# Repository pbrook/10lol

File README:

10LOL display board (10mm rgb led charlieplexed display matrix)
====

Hardware designs and firmware for a modular matrix display board.

Each module consists of an LED carrier board and a driver board.

Supply voltage is 7-20V (with onboard switching regulator).
TODO: Figure out actual power requirements, and if a single regulator can power
multiple modules.

The control board 
Modules operate autonomously,  module operates autonomously, accepting data over SPI.
The modules can be programmed with unique addresses, allowing
multiple modules on a single SPI bus.

SPI communication protocol
====

Commands are 4 bytes.  The first byte identidies the command, followed by 3
bytes of argument data (d0-d2).

On power-up the board will be in disconnected state.  A disconnect command
followed by a connect command should be used to ensure the serial interface
is coherent, and the board is in the ready state.

Command 0xe1 puts the specified board into the active state (other
previously active boards return to the ready state).

Commands <0xd0 are ignored when the board is not active.

Commands are as follows:

0x00 - 0x3f: Write pixel
 Pixels numbered left-right,then top-bottom)
  d0: red
  d1: green
  d2: blue

0x80: Page flip
 Set the framebuffer page for both display and pixel writing.
 This allows double buffered updates
  d0: Unused(0)
  d1: display page number
  d2: pixel write page number

0xa0: Initialize FORTH
 Initialize and enable the FORTH interpreter.
 The forth dictionary is stored at the end of the framebuffer.
  d0: rstack size (cells)
  d1: Dictionary size (in 256-byte framebuffer pages)
  d2: Unused (0)

0xa1: FORTH source
 Send one to three bytes of FORTH source code.  Null (0) characters are ignored.
  d0: First character
  d1: Second character
  d2: Third character

0xc0: Set brightness
 Sets brightness/color ballance (stored in EEPROM)
  d0: Red brightness
  d1: Green brightness
  d2: Blue brightness

0xd0: Set board address
 Modifies the board address (stored in EEPROM).
 The board will only respond to this address if the SDA pin is pulled low.
 This allows the addresses to be set without disconnecting the board.
  d0: 0xf5
  d1: 0xf0 + high address nibble
  d2: 0xf0 + low address nibble

0xe0: Connect
 Prepares the board for other commands
  d0: 0xf0
  d1: 0xf1
  d2: 0xf2

0xe1: Board select
 Only the selected board will respond to most commands.
  d0: board address (0xff to select all boards)
  d1: Unused (0)
  d2: Unused (0)

0xff: Disconnect
 Reset serial interface.
 The connect command must be sent before any other commands.
 The data bytes on this command are optional.  However sending the full
 sequence bytes ensures that the board is preoperly aligned with the
 four byte command boundary.
  d0: 0xff
  d1: 0xff
  d2: 0xff

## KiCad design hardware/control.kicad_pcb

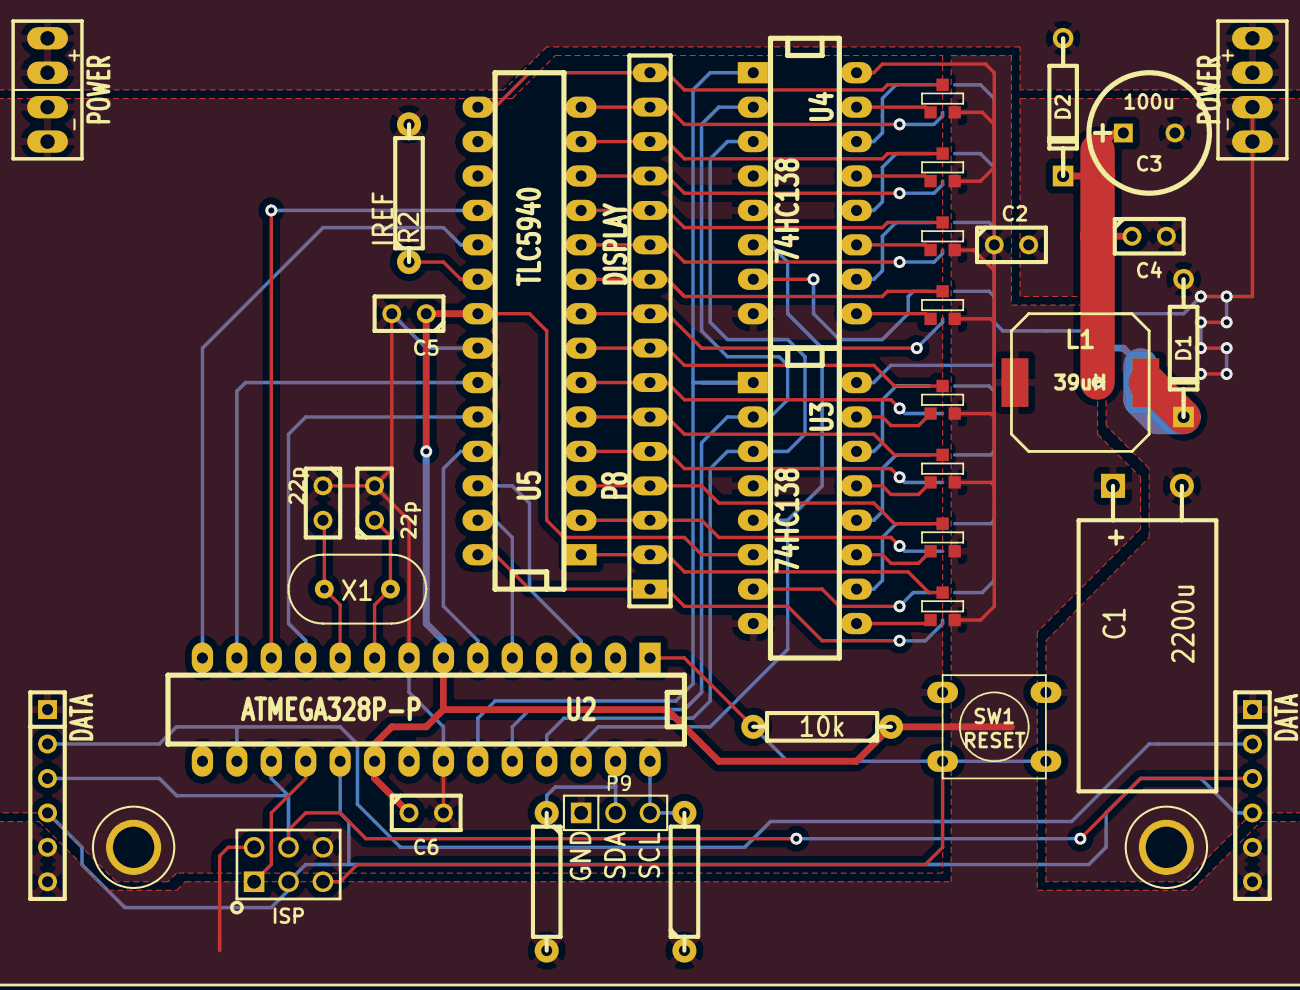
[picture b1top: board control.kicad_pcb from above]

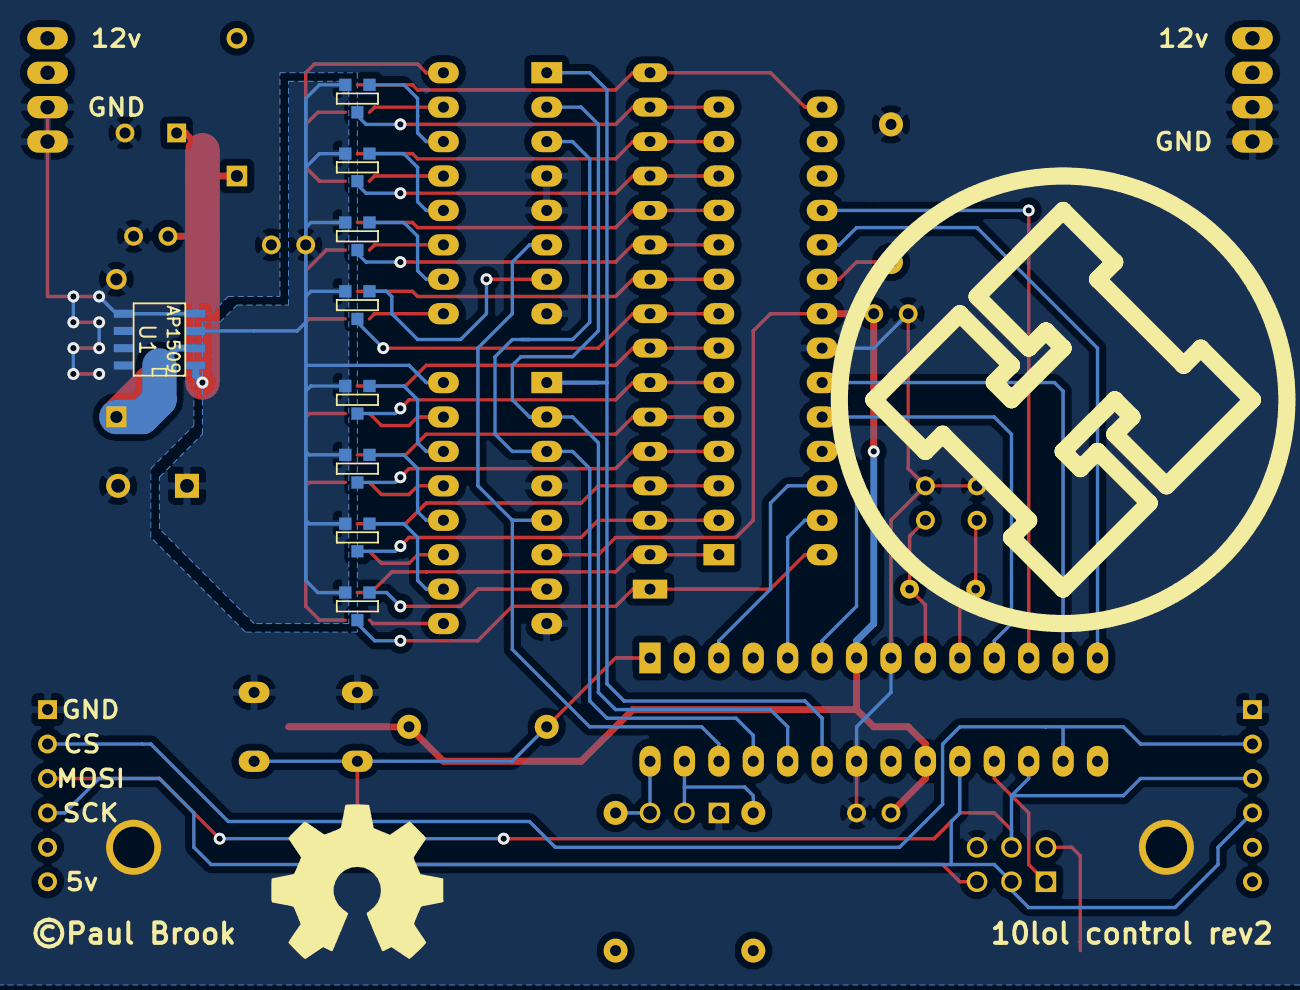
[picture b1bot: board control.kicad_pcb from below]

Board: 2 copper layers, 48 parts (10 on the bottom side), 58 nets.

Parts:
C1: 2200u; CPR10X20
C2, C4, C5, C6: 100n; C1
C3: 100u; C1.5V8V
C8, C9: 22p; C1
D1, D2: SR104; DO-41
HACKSPACE_LOGO: VAL**; HACKSPACE_LOGO
L1: 39uH; self_cms_we-tpc_XL
P1, P2: POWER; power2
P3, P4: DATA; SIL-6
P5: ISP; isp
P6, P7: CONN_1; HOLE3
P8: DISPLAY; SIL-16-ELL
P9: I2C; PIN_ARRAY_3X1
Q1, Q2, Q3, Q4, Q5, Q6, Q7, Q8, Q9, Q10, Q11, Q12, Q13, Q14, Q15, Q16: NX2301P; SOT23GDS_NP
R1: 10k; R4-LARGE_PADS
R2: IREF; R4-LARGE_PADS
R3: SDA; R4-LARGE_PADS
R4: SCL; R4-LARGE_PADS
SW1: RESET; SW_PUSH_SMALL
U1: AP1509; SO8E
U2: ATMEGA328P-P; DIP-28__300_ELL
U3, U4: 74HC138; DIP-16__300_ELL
U5: TLC5940; DIP-28__300_ELL
X1: 16MHz; Crystal

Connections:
/5v: C1.1, C2.1, C5.1, C6.1, L1.1, P3.5, P3.6, P4.5, P4.6, P5.2, Q1.S, Q2.S, Q3.S, Q4.S, Q5.S, Q6.S, Q7.S, Q8.S, Q9.S, Q10.S, Q11.S, Q12.S, Q13.S, Q14.S, Q15.S, Q16.S, R1.1, R3.2, R4.1, U1.3, U2.7, U2.20, U3.6, U3.16, U4.16, U5.21
/12v: C3.1, C4.1, D2.2, U1.1
/A: P8.1, Q1.D, U5.28
/A0: U2.23, U3.1, U4.1
/A1: U2.24, U3.2, U4.2
/A2: U2.25, U3.3, U4.3
/A3: U2.26, U3.5, U4.6
/Ai: Q1.G, U3.7
/B: P8.2, Q2.D, U5.1
/BLANK: U2.13, U5.23
/Bi: Q2.G, U3.9
/C: P8.3, Q3.D, U5.2
/CS: P3.2, P4.2, U2.16
/Ci: Q3.G, U3.10
/D: P8.4, Q4.D, U5.3
/DCPRG: U2.14, U5.19
/Di: Q4.G, U3.11
/E: P8.5, Q5.D, U5.4
/Ei: Q5.G, U3.12
/F: P8.6, Q6.D, U5.5
/Fi: Q6.G, U3.13
/G: P8.7, Q7.D, U5.6
/GND: C1.2, C2.2, C3.2, C4.2, C5.2, C6.2, C8.2, C9.1, D1.1, P1.1, P2.1, P3.1, P4.1, P5.6, P6.1, P7.1, P9.1, R2.2, SW1.1, U1.4, U1.5, U1.6, U1.7, U1.8, U2.8, U2.22, U3.4, U3.8, U4.4, U4.5, U4.8, U5.22
/GSCLK: U2.12, U5.18
/Gi: Q7.G, U3.14
/H: P8.8, Q8.D, U5.7
/Hi: Q8.G, U3.15
/IREF: R2.1, U5.20
/J: P8.9, Q9.D, U5.8
/Ji: Q9.G, U4.7
/K: P8.10, Q10.D, U5.9
/Ki: Q10.G, U4.9
/M: P8.11, Q11.D, U5.10
/MISO: P5.1, U2.18
/MOSI: P3.3, P4.3, P5.4, U2.17
/Mi: Q11.G, U4.10
/N: P8.12, Q12.D, U5.11
/Ni: Q12.G, U4.11
/P: P8.13, Q13.D, U5.12
/Pi: Q13.G, U4.12
/Q: P8.14, Q14.D, U5.13
/Qi: Q14.G, U4.13
/R: P8.15, Q15.D, U5.14
/RESET: P5.5, R1.2, SW1.2, U2.1
/Ri: Q15.G, U4.14
/S: P8.16, Q16.D, U5.15
/SCK: P3.4, P4.4, P5.3, U2.19
/SCL: P9.3, R4.2, U2.28
/SCLK: U2.6, U5.25
/SDA: P9.2, R3.1, U2.27
/SIN: U2.3, U5.26
/Si: Q16.G, U4.15
/VPRG: U2.5, U5.27
/XLAT: U2.11, U5.24
/out: D1.2, L1.2, U1.2
/raw: D2.1, P1.2, P2.2
unnamed: C9.2, U2.10, X1.1
unnamed: C8.1, U2.9, X1.2

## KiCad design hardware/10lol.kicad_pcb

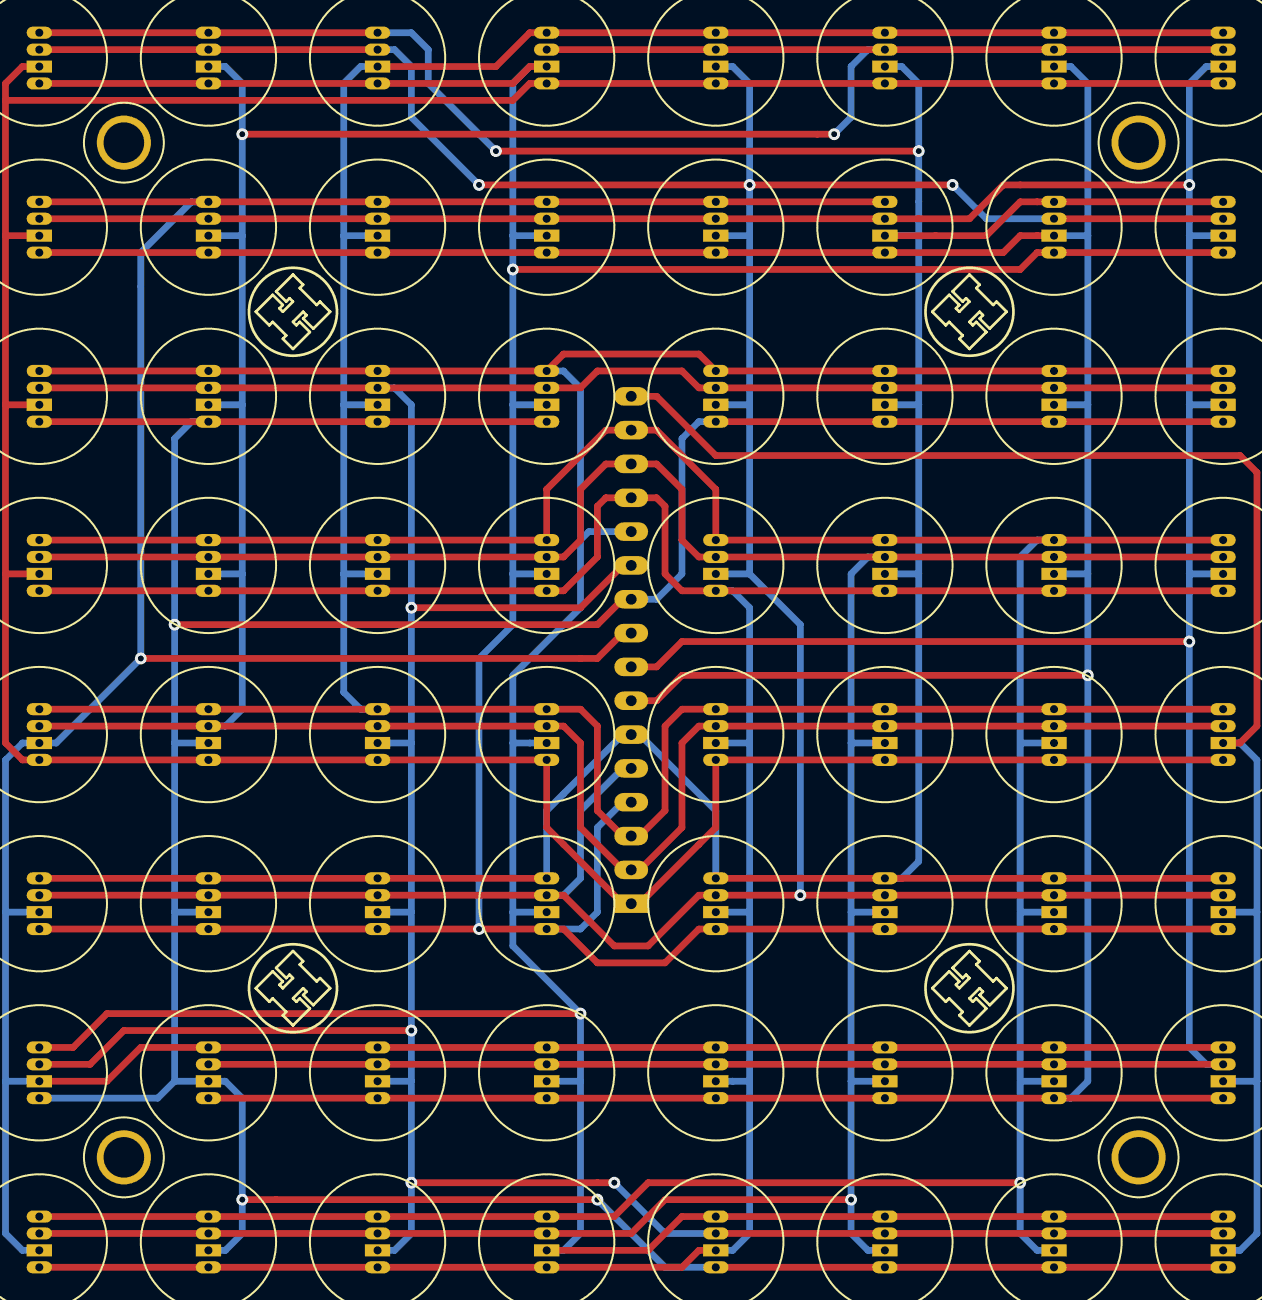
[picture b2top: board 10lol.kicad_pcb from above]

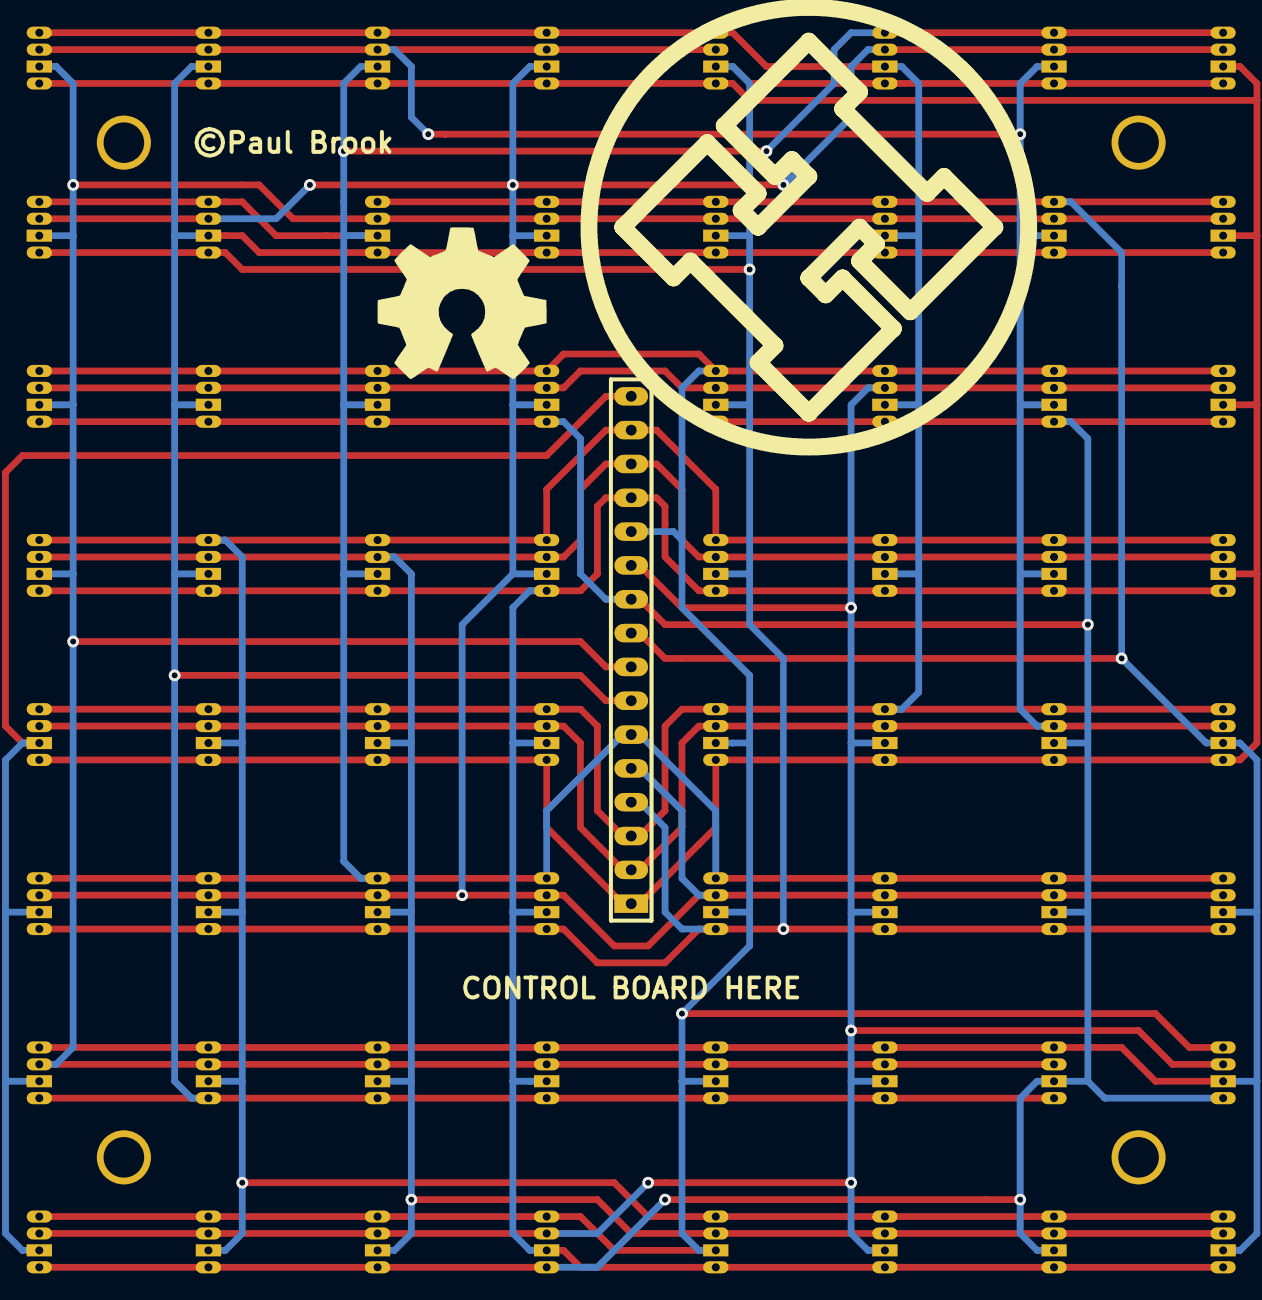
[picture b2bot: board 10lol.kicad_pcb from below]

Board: 2 copper layers, 74 parts (2 on the bottom side), 16 nets.

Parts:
D1, D2, D3, D4, D5, D6, D7, D8, D9, D10, D11, D12, D13, D14, D15, D16, D17, D18, D19, D20, D21, D22, D23, D24, D25, D26, D27, D28, D29, D30, D31, D32, D33, D34, D35, D36, D37, D38, D39, D40, D41, D42, D43, D44, D45, D46, D47, D48, D49, D50, D51, D52, D53, D54, D55, D56, D57, D58, D59, D60, D61, D62, D63, D64: RGBLED; RGB_LED_10_S
HACKSPACE_LOGO: VAL**; HACKSPACE_LOGO
LOGO_SMALL1: LOGO_S1; LOGO_SMALL
LOGO_SMALL2: LOGO_S2; LOGO_SMALL
LOGO_SMALL3: LOGO_S3; LOGO_SMALL
LOGO_SMALL4: LOGO_S4; LOGO_SMALL
P1: CONN_16; SIL-16-ELL
P2, P3, P4, P5: CONN_1; HOLE3

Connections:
/A: D1.2, D2.2, D3.2, D4.2, D5.1, D13.1, D21.1, D25.1, D29.1, D33.1, D37.1, D41.1, D45.1, D49.1, D53.1, D57.1, D61.1, P1.1
/B: D5.3, D9.2, D10.2, D11.2, D12.2, D13.3, D21.3, D25.3, D29.3, D33.3, D37.3, D41.3, D45.3, D49.3, D53.3, D57.3, D61.3, P1.2
/C: D5.4, D13.4, D17.2, D18.2, D19.2, D20.2, D21.4, D25.4, D29.4, D33.4, D37.4, D41.4, D45.4, D49.4, D53.4, D57.4, D61.4, P1.3
/D: D1.1, D6.1, D9.1, D14.1, D17.1, D22.1, D25.2, D26.2, D27.2, D28.2, D30.1, D38.1, D46.1, D50.1, D54.1, D58.1, D62.1, P1.4
/E: D1.3, D6.3, D9.3, D14.3, D17.3, D22.3, D30.3, D33.2, D34.2, D35.2, D36.2, D38.3, D46.3, D50.3, D54.3, D58.3, D62.3, P1.5
/F: D1.4, D6.4, D9.4, D14.4, D17.4, D22.4, D30.4, D38.4, D41.2, D42.2, D43.2, D44.2, D46.4, D50.4, D54.4, D58.4, D62.4, P1.6
/G: D2.1, D10.1, D15.1, D18.1, D23.1, D26.1, D31.1, D34.1, D39.1, D42.1, D47.1, D49.2, D50.2, D51.2, D52.2, D55.1, D63.1, P1.7
/H: D2.3, D10.3, D15.3, D18.3, D23.3, D26.3, D31.3, D34.3, D39.3, D42.3, D47.3, D55.3, D57.2, D58.2, D59.2, D60.2, D63.3, P1.8
/J: D2.4, D5.2, D6.2, D7.2, D8.2, D10.4, D15.4, D18.4, D23.4, D26.4, D31.4, D34.4, D39.4, D42.4, D47.4, D55.4, D63.4, P1.9
/K: D3.1, D7.1, D11.1, D13.2, D14.2, D15.2, D16.2, D19.1, D27.1, D35.1, D40.1, D43.1, D48.1, D51.1, D56.1, D59.1, D64.1, P1.10
/M: D3.3, D7.3, D11.3, D19.3, D21.2, D22.2, D23.2, D24.2, D27.3, D35.3, D40.3, D43.3, D48.3, D51.3, D56.3, D59.3, D64.3, P1.11
/N: D3.4, D7.4, D11.4, D19.4, D27.4, D29.2, D30.2, D31.2, D32.2, D35.4, D40.4, D43.4, D48.4, D51.4, D56.4, D59.4, D64.4, P1.12
/P: D4.1, D8.1, D12.1, D16.1, D20.1, D24.1, D28.1, D32.1, D36.1, D37.2, D38.2, D39.2, D40.2, D44.1, D52.1, D60.1, P1.13
/Q: D4.3, D8.3, D12.3, D16.3, D20.3, D24.3, D28.3, D32.3, D36.3, D44.3, D45.2, D46.2, D47.2, D48.2, D52.3, D60.3, P1.14
/R: D4.4, D8.4, D12.4, D16.4, D20.4, D24.4, D28.4, D32.4, D36.4, D44.4, D52.4, D53.2, D54.2, D55.2, D56.2, D60.4, P1.15
/S: D61.2, D62.2, D63.2, D64.2, P1.16

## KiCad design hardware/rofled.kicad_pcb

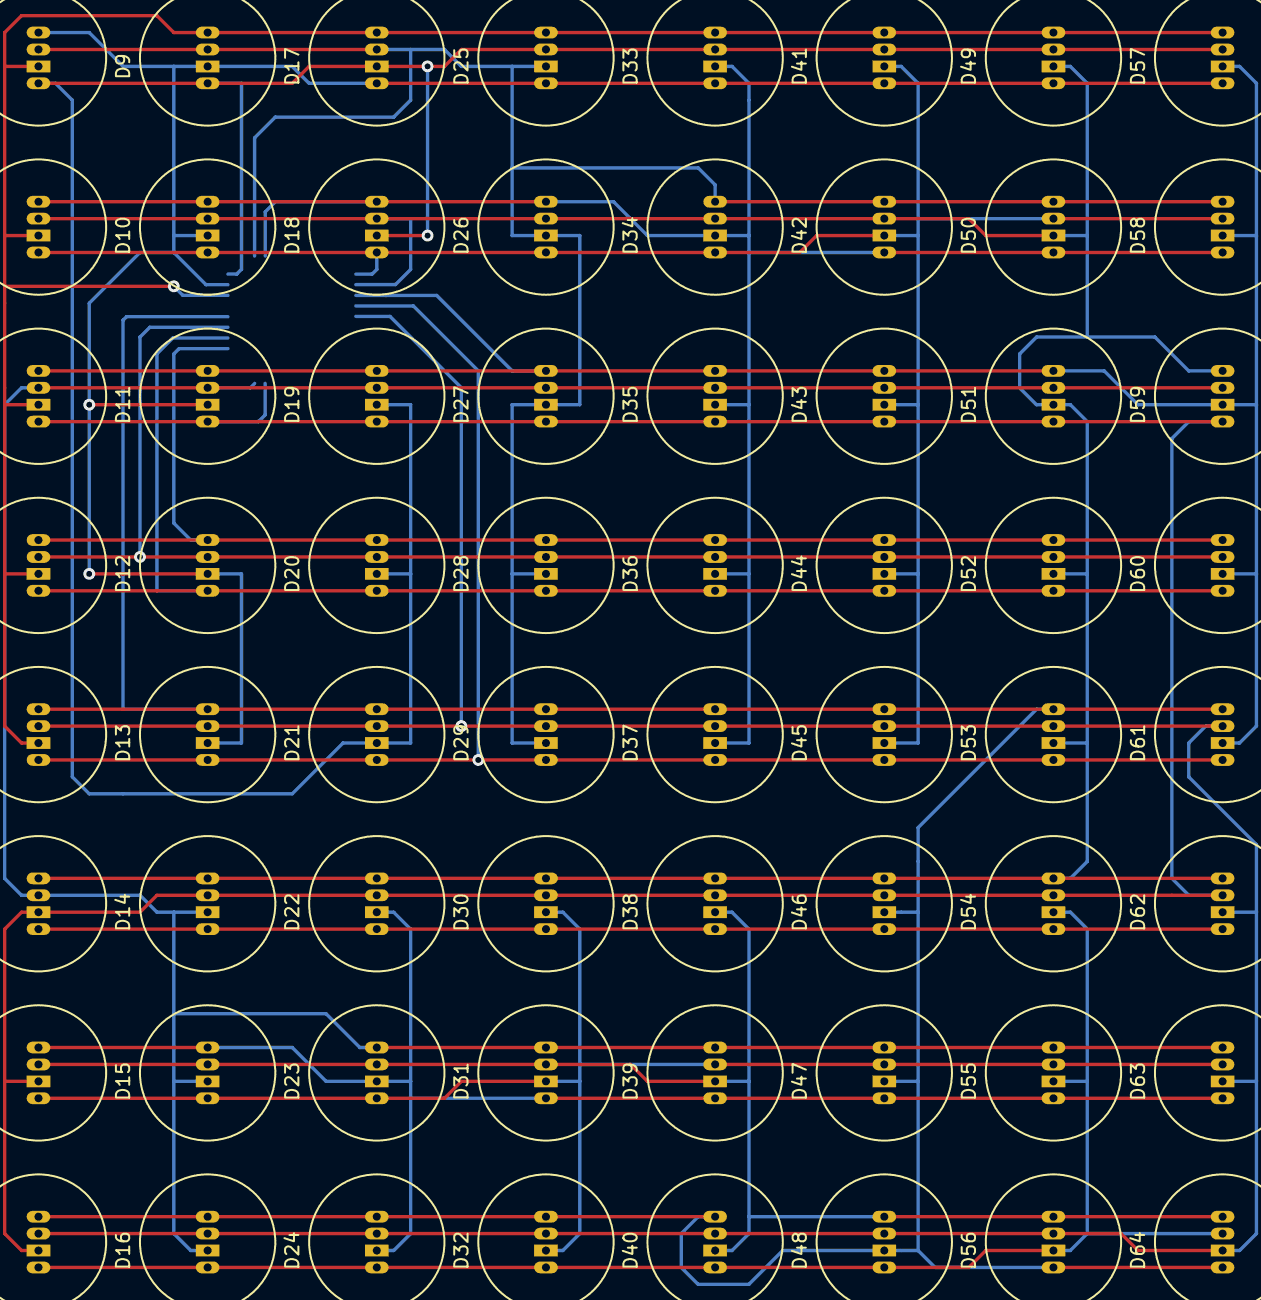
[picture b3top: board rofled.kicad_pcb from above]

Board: 2 copper layers, 65 parts (1 on the bottom side), 16 nets.

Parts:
D1, D2, D3, D4, D5, D6, D7, D8, D9, D10, D11, D12, D13, D14, D15, D16, D17, D18, D19, D20, D21, D22, D23, D24, D25, D26, D27, D28, D29, D30, D31, D32, D33, D34, D35, D36, D37, D38, D39, D40, D41, D42, D43, D44, D45, D46, D47, D48, D49, D50, D51, D52, D53, D54, D55, D56, D57, D58, D59, D60, D61, D62, D63, D64: RGBLED; RGB_LED_10
IC1: ATMEGA328P-A; TQFP32

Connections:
/A: D1.2, D2.2, D3.2, D4.2, D5.2, D9.4, D17.4, D25.4, D33.4, D41.4, D49.4, D57.4, IC1.30
/B: D1.4, D9.2, D10.2, D11.2, D12.2, D13.2, D17.1, D25.1, D33.1, D41.1, D49.1, D57.1, IC1.31
/C: D1.1, D9.1, D17.2, D18.2, D19.2, D20.2, D21.2, D25.3, D33.3, D41.3, D49.3, D57.3, IC1.32
/D: D1.3, D9.3, D17.3, D25.2, D26.2, D27.2, D28.2, D29.2, D34.4, D42.4, D50.4, D58.4, IC1.1
/E: D2.4, D10.4, D18.4, D26.4, D33.2, D34.2, D35.2, D36.2, D37.2, D42.1, D50.1, D58.1, IC1.2
/F: D2.1, D10.1, D18.1, D26.1, D34.1, D41.2, D42.2, D43.2, D44.2, D45.2, D50.3, D58.3, IC1.9
/G: D2.3, D6.4, D10.3, D14.4, D18.3, D22.4, D26.3, D30.4, D34.3, D38.4, D42.3, D46.4, D49.2, D50.2, D51.2, D52.2, D53.2, D54.4, D59.4, D62.4, IC1.10
/H: D3.4, D6.1, D11.4, D14.1, D19.4, D22.1, D27.4, D30.1, D35.4, D38.1, D43.4, D46.1, D51.4, D54.1, D57.2, D58.2, D59.2, D60.2, D61.2, D62.1, IC1.11
/J: D3.1, D6.2, D7.2, D8.2, D11.1, D14.3, D19.1, D22.3, D27.1, D30.3, D35.1, D38.3, D43.1, D46.3, D51.1, D54.3, D59.1, D62.3, IC1.23
/K: D3.3, D6.3, D11.3, D14.2, D15.2, D16.2, D19.3, D23.4, D27.3, D31.4, D35.3, D39.4, D43.3, D47.4, D51.3, D55.4, D59.3, D63.4, IC1.24
/M: D4.4, D7.4, D12.4, D15.4, D20.4, D22.2, D23.2, D24.2, D28.4, D31.1, D36.4, D39.1, D44.4, D47.1, D52.4, D55.1, D60.4, D63.1, IC1.25
/N: D4.1, D7.1, D12.1, D15.1, D20.1, D23.1, D28.1, D30.2, D31.2, D32.2, D36.1, D39.3, D44.1, D47.3, D52.1, D55.3, D60.1, D63.3, IC1.26
/P: D4.3, D7.3, D12.3, D15.3, D20.3, D23.3, D28.3, D31.3, D36.3, D38.2, D39.2, D40.2, D44.3, D48.4, D52.3, D56.4, D60.3, D64.4, IC1.27
/Q: D5.4, D8.4, D13.4, D16.4, D21.4, D24.4, D29.4, D32.4, D37.4, D40.4, D45.4, D46.2, D47.2, D48.2, D53.4, D56.1, D61.4, D64.1, IC1.28
/R: D5.1, D8.1, D13.1, D16.1, D21.1, D24.1, D29.1, D32.1, D37.1, D40.1, D45.1, D48.1, D53.1, D54.2, D55.2, D56.2, D61.1, D64.3, IC1.12
/S: D5.3, D8.3, D13.3, D16.3, D21.3, D24.3, D29.3, D32.3, D37.3, D40.3, D45.3, D48.3, D53.3, D56.3, D61.3, D62.2, D63.2, D64.2, IC1.13

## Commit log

2014-04-23 Production hardware
2014-04-23 Initial firmware checkin.
2014-04-28 Assembly interrupt handle
2014-05-03 Per board and global page flip.
2014-05-03 Common anode support
2014-05-05 Add test LED config.
2014-05-12 Split out control board. Simplify LED board.
2014-05-12 Create control board PCB. Finish LED board layout.
2014-05-12 Remove stray solder mask region
2014-05-13 Improve charlieplex generator
2014-05-25 Use driver chips
2014-05-31 Modify based on actual hardware results.
2014-06-03 Handle CPU overload (relatively) gracefully
2014-06-03 Better demo
2014-06-14 Rewrite command handling
2014-06-17 Add forth support
2014-06-23 Tweak address latching code and default brightness
2014-06-23 Final hardware tweaks.
2014-07-08 Serial tweaks
    Process incoming data first. Reset link on invalid command.
2014-07-08 Fix reset glitch
2014-07-08 Disable unused peripherals
2014-07-08 Sleep mode
2014-07-08 Deeper sleep when off
2014-07-17 Fix race condition in sleep code
2014-07-18 Add example code
2014-07-18 Clear display on exit
2014-07-19 Add white test
2014-07-20 Fix forth support
2014-07-20 Native SPI support
2014-07-20 Fix plasma slowness
2014-07-20 Ignore python2 compiled files
2014-07-20 Fix serial driver
2014-07-20 Scrolly text
2014-08-08 PCB fixes.
    Tweak power plane. Move mounting holes. Fix soldermask on power
    connector.
2014-08-08 SMD inductor

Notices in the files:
hardware/10lol.kicad_pcb:
©Paul Brook
